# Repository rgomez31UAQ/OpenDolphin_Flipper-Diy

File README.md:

🐬 OpenDolphin

A fully open-source hardware implementation inspired by Flipper Zero.

Welcome to OpenDolphin! This repository contains the PCB design files, schematics, and Bill of Materials (BOM) for a DIY, Flipper Zero-compatible multi-tool. Designed by Dolphinos27.
Overview
This project is currently under active development

⚠️ Disclaimer

This project is for educational and research purposes only. The author (Dolphinos27) is not responsible for any misuse or damage caused by this device. Please comply with your local radio frequency and digital privacy laws.
📜 License

This project is licensed under the MIT License - see the LICENSE file for details.

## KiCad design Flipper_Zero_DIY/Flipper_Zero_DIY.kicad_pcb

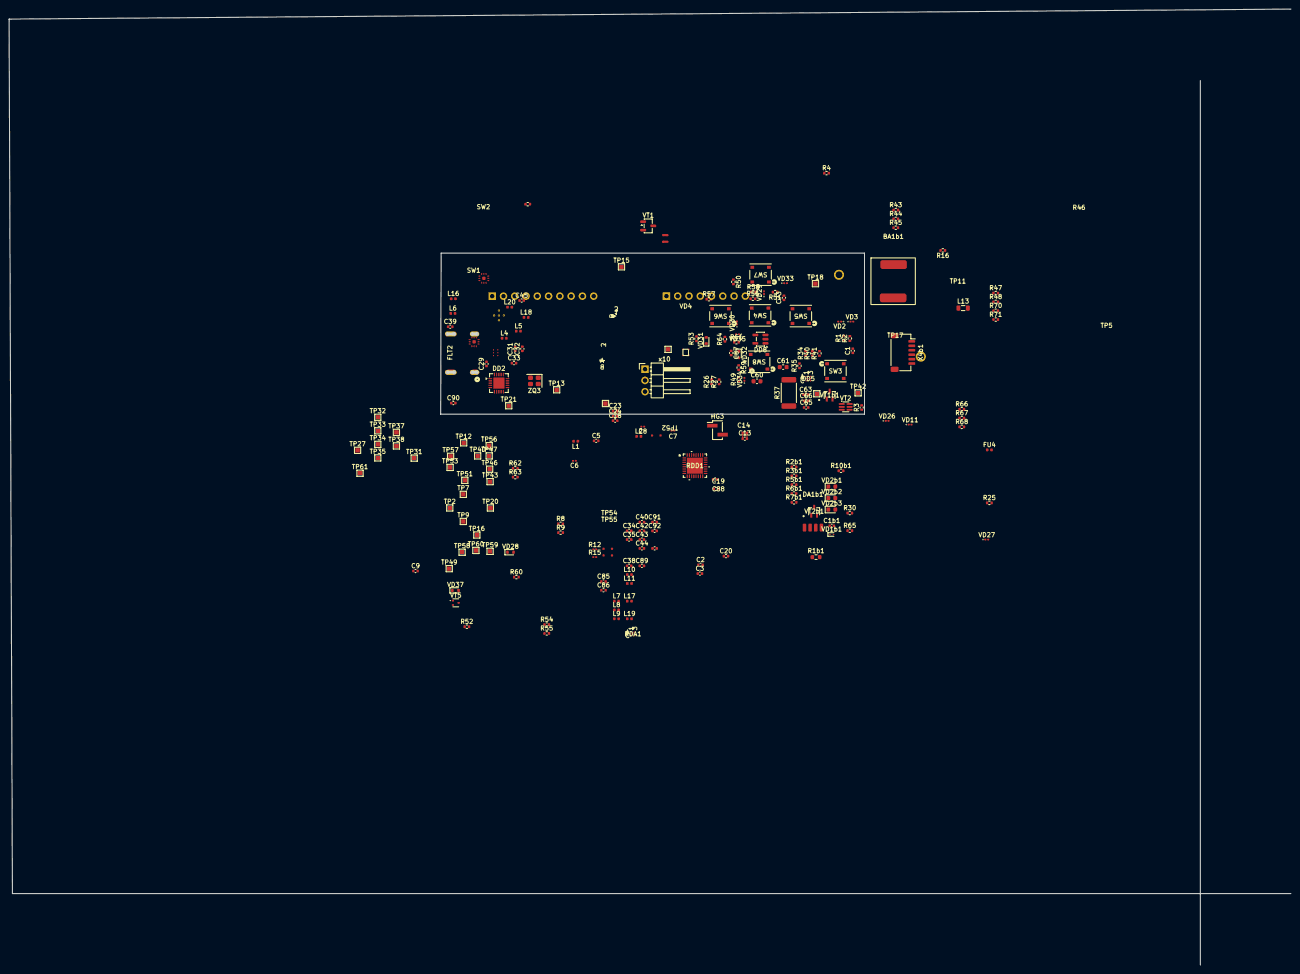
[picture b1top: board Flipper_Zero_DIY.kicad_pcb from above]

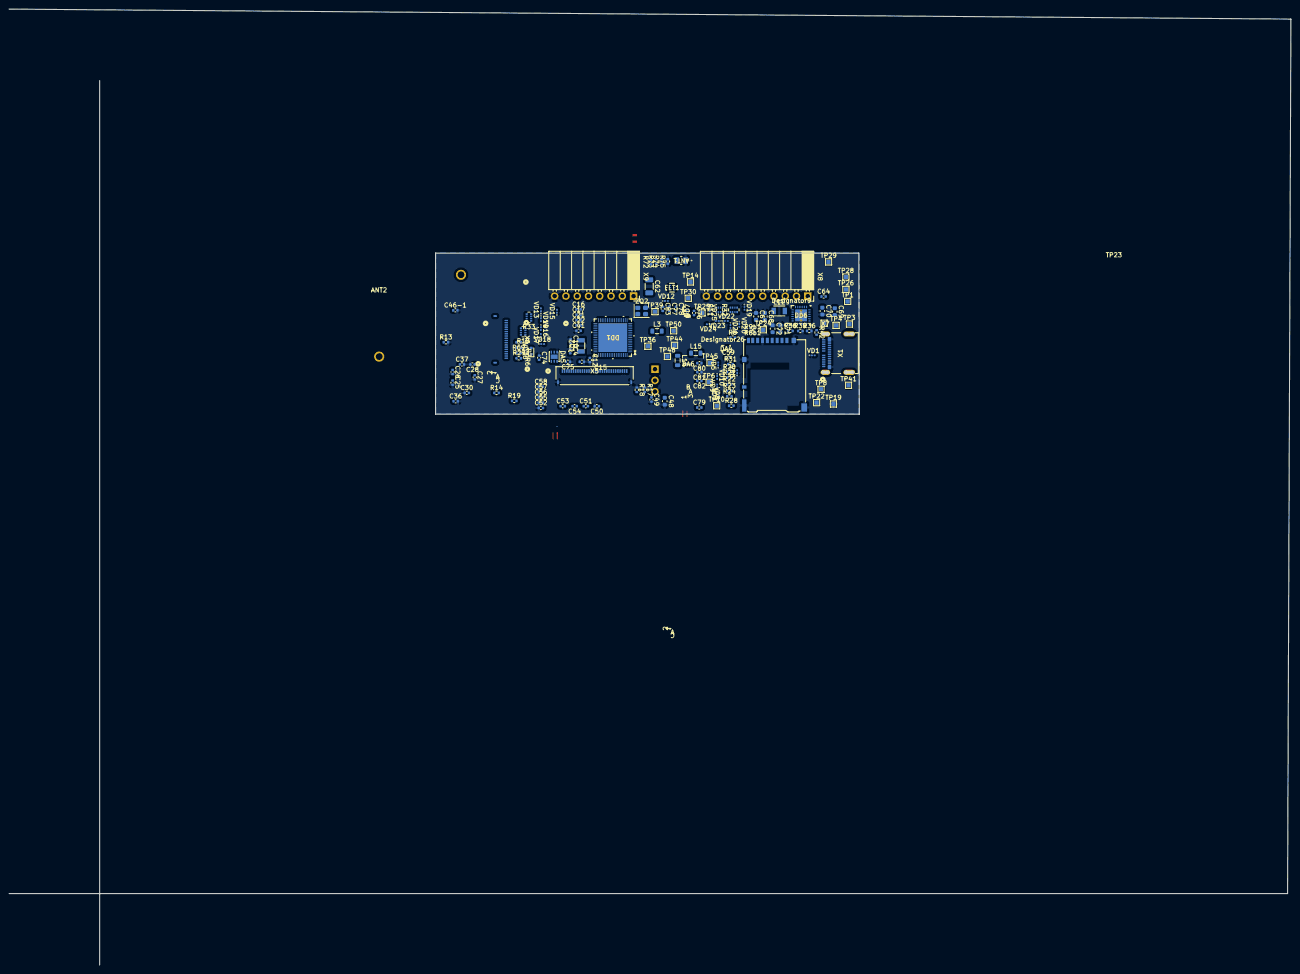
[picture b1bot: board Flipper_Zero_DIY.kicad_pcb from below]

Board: 2 copper layers, 288.8 x 215.3 mm, 342 parts (144 on the bottom side), 195 nets.

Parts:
ANT1: 1001312; ANT_1001312_AVX
ANT2: Sub-1GHz Antenna A5; Antenna_2
BA1b1: AST0760MCTRQ; Buzzer_539-AST0760MCTRQ
C1, C1b1, C12, C13, C14, C18, C22, C24, C25, C26, C27, C28, C30, C36, C37, C41, C49, C85, C88: 100nF; C_0402_1005Metric
C2, C3, C31, C39, C40, C44, C50, C51, C52, C53, C55, C56, C57, C58, C89, C90, C92: DNP; C_0402_1005Metric
C4, C10: 18pF; C_0402_1005Metric
C5: 0.8pF; C_0402_1005Metric
C6: 0.3pF; C_0201_0603Metric
C7: 1.5pF; C_0201_0603Metric
C8: DNP; C_0201_0603Metric
C9, C80, C83, C86, C87: 10uF; C_0402_1005Metric
C15, C19, C20, C73, C77, C81: 4.7uF; C_0402_1005Metric
C16, C21, C59, C63, C74, C75: 1uF; C_0402_1005Metric
C17: 10nF; C_0402_1005Metric
C23, C29, C38, C46-1, C46-2: 100pF; C_0402_1005Metric
C32: 1.2pF; C_0402_1005Metric
C33: 0.6pF; C_0402_1005Metric
C34, C35: 9pF; C_0402_1005Metric
C42, C43: 10pF; C_0402_1005Metric
C45: 8.2pF; C_0402_1005Metric
C48, C60, C61, C67, C68, C70, C71, C72: 10uF; C_0603_1608Metric
C54, C66, C76, C78, C79, C82: 2.2uF; C_0402_1005Metric
C62: DNP; C_1206_3216Metric
C64: 47nF; C_0402_1005Metric
C65: 470nF; C_0402_1005Metric
C69: 1uF; C_0603_1608Metric
C91: 22pF; C_0402_1005Metric
DA1b1: TSOP75338TR
DA4: LP5562TMX/NOPB; LP5562TMX-NOPB
DA5: ADP151ACPZ-3.3-R7; LFCSP-6-1EP_2x2mm_P0.65mm_EP1x1.6mm
DA6: LM3281YFQR
DD1: STM32WB55RGV6TR
DD2: QFN-20-1EP_4x4mm_P0.5mm_EP2.5x2.5mm
DD5: BQ27220YZFR
DD6: BQ25896RTWR
DD7: LM3281YFQR
DD8: NC7SZ125M5X; SOT-23-5
FLT1: LFL182G45TC1A108
FLT2: B0310J50100AHF; 0805_6PIN_PACKAGE
FU4: ERB-RD2R00X; Fuse_0402_1005Metric
HG3: ERC12864FAMF03-1-S7; PinHeader_1x02_P2.00mm_Vertical_SMD_Pin1Left
L1, L11: 2.7nH; L_0402_1005Metric
L2: 3nH; L_0402_1005Metric
L3: 10uH; L_0805_2012Metric
L4: 3.3nH; L_0402_1005Metric
L5: 6.8nH; L_0402_1005Metric
L6, L7, L8, L18, L20: 0; L_0402_1005Metric
L9: 2.2nH; L_0402_1005Metric
L10: DNP; L_0402_1005Metric
L12: 1uH; L_TDK_NLV25_2.5x2.0mm
L13, L14, L15: 470nH; L_0805_2012Metric
L16: 56nH; L_0402_1005Metric
L17: 22nH; L_0402_1005Metric
L19: 27nH; L_0402_1005Metric
R1, R2: 5.1k; R_0402_1005Metric
R1b1: 22; R_0603_1608Metric
R2b1, R6b1, R23, R31: 150; R_0402_1005Metric
R3: 100k; C_0402_1005Metric
R3b1, R8b1, R34, R35, R44, R46, R47, R49, R50, R51, R53, R61, R62: 10k; R_0402_1005Metric
R4, R60, R64: 100k; R_0402_1005Metric
R5, R17, R18, R43, R52, R65, R66, R67, R73, R74, R75: DNP; R_0402_1005Metric
R5b1, R9b1, R10b1: 39; R_0402_1005Metric
R6, R7, R24, R26, R28, R29: 51; R_0402_1005Metric
R7b1: 10; R_0402_1005Metric
R8, R9: 22; R_0402_1005Metric
R10, R11, R32, R33: 51; R_Array_Convex_4x0402
R12, R15: 0; R_0201_0603Metric
R13: 56k; R_0402_1005Metric
R14, R54, R55, R56, R57, R58, R59: 330; R_0402_1005Metric
R16, R70: 1.5; R_0402_1005Metric
R19, R20, R25, R27, R30, R72: 0; R_0402_1005Metric
R21, R22, R68: 47k; R_0402_1005Metric
R36: 470; R_0402_1005Metric
R37: 10m; R_2512_6332Metric
R38: 5.23k; R_0402_1005Metric
R39: 30.1k; R_0402_1005Metric
R40, R41: 1.5k; R_0402_1005Metric
R42: 4.7k; R_0402_1005Metric
R45: 100; R_0402_1005Metric
R48, R71: 3.3; R_0402_1005Metric
R63: 510; R_0402_1005Metric
R69: 1k; R_0402_1005Metric
RDA1: FAN48610BUC50X; WLCSP9_1P2X1P2_ONS
RDD1: ST25R3916-AQWT; VFQFPN32_5X5_WETTABLE_STM
SB5, SB6: Net Tie; NetTie-2_SMD_Pad0.5mm
SW1: SKY13373-460LF; QFN-12-2x2mm_equal_distribution
SW2: QFN-12-2x2mm_equal_distribution
SW3, SW4, SW5, SW6, SW7, SW8: SKRMAAE010; SKRMAAE010_AAL
TP1: STAT; TestPoint_Pad_1.0x1.0mm
TP2: PG; TestPoint_Pad_1.0x1.0mm
TP3: PWR_INT; TestPoint_Pad_1.0x1.0mm
TP4: OTG; TestPoint_Pad_1.0x1.0mm
TP5: GPOUT; TestPoint_Pad_1.0x1.0mm
TP6: TEMP; TestPoint_Pad_1.0x1.0mm
TP7: 3V32; TestPoint_Pad_1.0x1.0mm
TP8: 5V1; TestPoint_Pad_1.0x1.0mm
TP9: 5V2; TestPoint_Pad_1.0x1.0mm
TP10: BAT1; TestPoint_Pad_1.0x1.0mm
TP11: BAT2; TestPoint_Pad_1.0x1.0mm
TP12: SYS1; TestPoint_Pad_1.0x1.0mm
TP13: SYS2; TestPoint_Pad_1.0x1.0mm
TP14: EXT3V3; TestPoint_Pad_1.0x1.0mm
TP15: EXT3V32; TestPoint_Pad_1.0x1.0mm
TP16: LDO1; TestPoint_Pad_1.0x1.0mm
TP17: LDO2; TestPoint_Pad_1.0x1.0mm
TP18: GND1; TestPoint_Pad_1.0x1.0mm
TP19: GND2; TestPoint_Pad_1.0x1.0mm
TP20: GND3; TestPoint_Pad_1.0x1.0mm
TP21: GND4; TestPoint_Pad_1.0x1.0mm
TP22: I2C_SDA; TestPoint_Pad_1.0x1.0mm
TP23: I2C_SCL; TestPoint_Pad_1.0x1.0mm
TP24: SWDIO; TestPoint_Pad_1.0x1.0mm
TP25: SWCLK; TestPoint_Pad_1.0x1.0mm
TP26: I2C_SCL2; TestPoint_Pad_1.0x1.0mm
TP27: I2C_SDA2; TestPoint_Pad_1.0x1.0mm
TP28: UART1_RX; TestPoint_Pad_1.0x1.0mm
TP29: UART1_TX; TestPoint_Pad_1.0x1.0mm
TP30: VIBRO; TestPoint_Pad_1.0x1.0mm
TP31: NFC_CS; TestPoint_Pad_1.0x1.0mm
TP32: RFID_CARRIER; TestPoint_Pad_1.0x1.0mm
TP33: IR_RX; TestPoint_Pad_1.0x1.0mm
TP34, TP60: IR_TX; TestPoint_Pad_1.0x1.0mm
TP35, TP57: SPEAKER; TestPoint_Pad_1.0x1.0mm
TP36, TP59: iBTN; TestPoint_Pad_1.0x1.0mm
TP37: RFID_IN; TestPoint_Pad_1.0x1.0mm
TP38: RFID_OUT; TestPoint_Pad_1.0x1.0mm
TP39: RFID_PULL; TestPoint_Pad_1.0x1.0mm
TP40: R_CLK; TestPoint_Pad_1.0x1.0mm
TP41: VBUS1; TestPoint_Pad_1.0x1.0mm
TP42: VBUS2; TestPoint_Pad_1.0x1.0mm
TP43: D-; TestPoint_Pad_1.0x1.0mm
TP44: D+; TestPoint_Pad_1.0x1.0mm
TP45: D_MI; TestPoint_Pad_1.0x1.0mm
TP46: R_MI; TestPoint_Pad_1.0x1.0mm
TP47: R_MO; TestPoint_Pad_1.0x1.0mm
TP48: D_MO; TestPoint_Pad_1.0x1.0mm
TP49: D_SCK; TestPoint_Pad_1.0x1.0mm
TP50: BOOT; TestPoint_Pad_1.0x1.0mm
TP51: NRST; TestPoint_Pad_1.0x1.0mm
TP52: BLE1; 2_TEST_PIN_1.35mm_pitch
TP53: CC_PWR; TestPoint_Pad_1.0x1.0mm
TP54: Balun; 2_TEST_PIN_1.35mm_pitch
TP55: SUB-1-GHz; 2_TEST_PIN_1.35mm_pitch
TP56: SYS; TestPoint_Pad_1.0x1.0mm
TP58: SPEAKER1; TestPoint_Pad_1.0x1.0mm
TP61: GND; TestPoint_Pad_1.0x1.0mm
VD1, VD2, VD3, VD11, VD13, VD14, VD15, VD16, VD17, VD18, VD19, VD20, VD21, VD22, VD23, VD24, VD25: ESD230B1W0201E6327XTSA1; D_0201_0603Metric
VD1b1: ESD230B1W0201E6327XT; D_SOD-923
VD2b1, VD2b2, VD2b3: VSMY14940; LED_0603_1608Metric
VD4: CLMUD-FKC-CHJNPM569ABB845343; SMD_RGB_LED_CLMUD-FKC-CHJNPM569ABB845343
VD5, VD6, VD7, VD8, VD9, VD10, VD12, VD26, VD27, VD29, VD30, VD33, VD34, VD35: ESD241B1W0201E6327XTSA1; D_0201_0603Metric
VD28, VD31, VD32: 1N4148X; D_SOD-523
VD36: 1N4148X-TP; D_SOD-523
VD37: DNP; D_SOD-523
VT1: DMP1045U-7; SOT-23-3
VT1b1, VT2b1: DMN2058UW-7; SOT323_DMN2058UW_DIO
VT2: MMDT2907A-7-F; SOT-363_SC-70-6
VT5: DMN313DLT-7; SOT-523
X1: 105450-0101; CONN_105450-0101_MOL
X4b1: 0.5-H2.0-6LT; JST_SH_SM06B-SRSS-TB_1x06-1MP_P1.00mm_Horizontal
X5: FH34SRJ-30S-0.5SH(50); CONN30x1_FH34SRJ-30S-0.5SH50_HIR
X6: FH34SRJ-18S-0.5SH(50); 18_pin_JST
X7: Micro_SD; microSD_HC_Hirose_DM3AT-SF-PEJM5
X8: 2.54-WT-1X10; PinSocket_1x10_P2.54mm_Horizontal
X9: 2.54-WT-1X8; PinSocket_1x08_P2.54mm_Horizontal
ZQ1: SF32K32768D31T-12.5; Crystal_SMD_3215-2Pin_3.2x1.5mm
ZQ2: CXD2-032000000-1010B; Crystal_SMD_2520-4Pin_2.5x2.0mm
ZQ3: CXD2-026000000-0810B; Crystal_SMD_2520-4Pin_2.5x2.0mm
x10: Connector 3P; PinHeader_1x03_P2.54mm_Horizontal

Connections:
+3V3: C9.2, C12.1, C13.1, C14.1, C15.1, C16.1, C17.1, C18.1, C19.1, C23.1, C24.1, C25.1, C26.1, C27.1, C28.1, C36.1, C37.1, C48.1, C49.1, C85.1, C88.1, DD1.14 (VDDA), DD1.30 (VDD), DD1.33 (VDDRF), DD1.44 (VDDSMPS), DD1.45 (VDD), DD1.55 (VDDUSB), DD1.68 (VDD), DD2.4 (DVDD), DD2.9 (AVDD), DD2.11 (AVDD), DD2.14 (AVDD), DD2.15 (AVDD), DD2.18 (DGUARD), DD8.5 (VCC), R5.2, R34.1, R40.1, R41.1, R42.1, R47.1, R48.2, R49.2, R50.2, R51.2, R52.2, R53.2, R62.2, R71.2, RDD1.1 (VDD_IO), SW1.6 (VDD), SW2.6 (VDD), SW4.2, TP7.1, TP53.1, VD26.2 (A2), X5.5, X5.6, X5.7, X5.8, X5.9, X5.10, X5.11, X5.12, X5.15, X6.3
+5V: RDA1.A1 (VOUT), RDA1.A2 (VOUT), RDD1.8 (VDD), RDD1.10 (VDD_TX)
BAT: C63.2, DD5.C1 (SRP), DD5.C3 (BAT), R37.2, TP10.1, TP11.1, x10.1
BUTTON_BACK: DD1.2 (PC13), DD6.12 (QON_N), R54.1
BUTTON_DOWN: DD1.50 (PC6), R59.1
BUTTON_LEFT: DD1.29 (PB11), R57.1
BUTTON_OK: DD1.5 (PH3), R55.1, TP50.1
BUTTON_RIGHT: DD1.46 (PB12), R56.1
BUTTON_UP: DD1.28 (PB10), R58.1
CC1101_CS: DD1.61 (PD0), DD2.7 (CSN)
CC1101_G0: DD1.16 (PA1), R14.2
DISPLAY_CS: DD1.59 (PC11), R17.2, X5.2
DISPLAY_DI: DD1.39 (PB1), X5.4
DISPLAY_RST: DD1.38 (PB0), R18.2, X5.3
GND: ANT1.1 (A), C1.2, C1b1.2, C2.1, C3.1, C4.1, C5.2, C6.2, C7.2, C8.1, C8.2, C9.1, C10.1, C12.2, C13.2, C14.2, C15.2, C16.2, C17.2, C18.2, C19.2, C20.2, C21.2, C22.2, C23.2, C24.2, C25.2, C26.2, C27.2, C28.2, C30.1, C31.2, C32.2, C34.1, C35.1, C36.2, C37.2, C39.1, C40.1, C41.1, C42.2, C43.2, C44.2, C45.2, C46-1.2, C46-2.2, C48.2, C49.2, C50.2, C52.1, C55.1, C56.1, C57.1, C58.1, C59.2, C60.1, C61.1, C63.1, C65.1, C66.1, C67.1, C68.1, C69.2, C70.2, C71.1, C72.1, C73.1, C74.1, C75.1, C77.1, C80.1, C81.1, C83.1, C85.2, C86.2, C87.2, C88.2, C89.1, C90.2, C91.2, C92.2, DA1b1.1 (GND), DA1b1.4 (GND), DA4.A3 (CLK_32K), DA4.B1 (ADDR_SEL1), DA4.B2 (ADDR_SEL0), DA4.B3 (GND), DA5.1 (GND), DD1.32 (VSSRF), DD1.42 (VSSSMPS), DD1.69 (EPAD), DD2.16 (GND), DD2.19 (GND), DD2.21 (EPAD), DD5.B2 (VSS), DD6.2 (PSEL), DD6.9 (CE_N), DD6.17 (PGND), DD6.18 (PGND), DD6.25 (PAD), DD8.3 (GND), FLT1.2 (GND), FLT1.5 (GND), FLT2.2 (GND), L2.2, L10.1, R1.2, R2.2, R3.1, R3b1.1, R4.1, R8b1.1, R13.2, R17.1, R18.1, R35.2, R36.2, R39.2, R43.1, R46.2, R61.1, R72.1, R72.2, R74.1, R74.2, R75.1, R75.2, RDA1.C1 (PGND), RDA1.C2 (PGND), RDA1.C3 (AGND), RDD1.6 (GND_D), RDD1.12 (GND_DR), RDD1.16 (GND_DR), RDD1.20 (I2C_EN), RDD1.21 (VSS), RDD1.26 (GND_A), RDD1.33 (EPAD), SB5.2, SB6.2, SW1.2 (GND), SW1.7 (GND), SW1.8 (GND), SW1.10 (GND), SW1.12 (GND), SW2.2 (GND), SW2.7 (GND), SW2.8 (GND), SW2.10 (GND), SW2.12 (GND), SW3.2, SW5.2, SW6.2, SW7.2, SW8.2, TP18.1, TP19.1, TP20.1, TP21.1, TP52.2, TP54.2, TP55.2, TP61.1, VD1.1 (A1), VD1b1.1 (A1), VD2.1 (A1), VD3.1 (A1), VD5.1 (A1), VD6.1 (A1), VD7.1 (A1), VD8.1 (A1), VD9.1 (A1), VD10.1 (A1), VD12.1 (A1), VD13.1 (A1), VD14.1 (A1), VD15.1 (A1), VD16.1 (A1), VD17.1 (A1), VD18.1 (A1), VD19.1 (A1), VD20.1 (A1), VD21.1 (A1), VD22.1 (A1), VD23.1 (A1), VD24.1 (A1), VD25.1 (A1), VD26.1 (A1), VD27.2 (A2), VD29.2 (A2), VD30.2 (A2), VD33.2 (A2), VD34.2 (A2), VD35.2 (A2), VT1b1.3 (S), VT2b1.3 (S), VT5.3 (S), X1.A1 (GND), X1.A12 (GND), X1.B1 (GND), X1.B12 (GND), X4b1.1, X5.16, X5.28, X5.29, X5.31, X5.32, X6.6, X6.8, X7.6 (VSS), X7.11 (SHIELD), X8.3, X8.10, X9.8, ZQ2.3, ZQ3.3, x10.3
GND1: C79.1, C82.1, DA6.A3 (EPAD), SB5.1
GND2: C76.1, C78.1, DD7.A3 (GND), SB6.1
I2C_SCL: DA4.C2 (SCL), DD1.24 (PA9), DD5.A3 (SCL), DD6.5 (SCL), R41.2, TP23.1
I2C_SDA: DA4.C1 (SDA), DD1.51 (PA10), DD5.A2 (SDA), DD6.6 (SDA), R40.2, TP22.1
IR_RX: DD1.15 (PA0), TP33.1, X6.17
IR_TX: DD1.7 (PB9), TP34.1, X6.16
LCD_LED: DA4.A1 (W), HG3.2
LDO_3.3V: C75.2, DA5.2 (VOUT), DD1.1 (VBAT), TP16.1, TP17.1
NFC_CS: DD1.40 (PE4), RDD1.29 (BSS), TP31.1, X6.4
unnamed: ANT2.1 (A), C90.1, R15.2, TP55.1
unnamed: BA1b1.2, R1b1.1
unnamed: C29.2, FLT2.3 (Bal)
unnamed: C31.1, L4.2, L5.1
unnamed: C32.1, L5.2, R12.1
unnamed: C38.2, FLT2.4 (Bal)
unnamed: C39.2, L6.1, L18.2
unnamed: C42.1, L7.2, L19.1
unnamed: C43.1, L8.1, L19.2
unnamed: C44.1, L9.2, R15.1
unnamed: C45.1, L11.1, L20.2
unnamed: C64.2, DD6.19 (SW), DD6.20 (SW), L12.1
unnamed: C89.2, L6.2, L16.1
unnamed: C91.1, L8.2, L17.1
unnamed: DA1b1.3 (OUT), X4b1.2
unnamed: C1b1.1, DA1b1.2 (Vs), R7b1.1
unnamed: DA4.A4 (B), R30.1
unnamed: DA4.B4 (G), R27.1
unnamed: DA4.C4 (R), R25.1
unnamed: C71.2, C72.2, C74.2, DA5.3 (VIN), DD5.C2 (SRN), DD6.13 (BAT), DD6.14 (BAT), R37.1
unnamed: C80.2, C81.2, C82.2, DA6.A1 (FB), L15.1, R16.2, R70.2
unnamed: DA6.B2 (SW), L14.1
unnamed: DD1.35 (OSC_IN), ZQ2.1
unnamed: DD1.34 (OSC_OUT), ZQ2.2
unnamed: DD1.20 (PA5), R6.2
unnamed: DD1.52 (PA11), R8.2, TP43.1
unnamed: DD1.53 (PA12), R5.1, R9.2, TP44.1
unnamed: DD1.65 (PB5), R7.1
unnamed: C4.2, DD1.3 (PC14), ZQ1.2
unnamed: C10.2, DD1.4 (PC15), ZQ1.1
unnamed: C5.1, DD1.31 (RF1), L1.1
unnamed: C20.1, DD1.41 (VFBSMPS), L3.1
unnamed: DD1.43 (VLXSMPS), L3.2
unnamed: C21.1, C22.1, DD1.13 (VREF+)
unnamed: C30.2, DD2.5 (DCOUPL)
unnamed: DD2.6 (GDO0), R14.1
unnamed: DD2.17 (RBIAS), R13.1
unnamed: C29.1, C33.1, DD2.13 (RF_N)
unnamed: C33.2, C38.1, DD2.12 (RF_P)
unnamed: C34.2, DD2.8 (XOSC_Q1), ZQ3.1
unnamed: C35.2, DD2.10 (XOSC_Q2), ZQ3.2
unnamed: DD5.B1 (BIN), R35.1
unnamed: DD5.A1 (GPOUT), R34.2, TP5.1
unnamed: C65.2, C66.2, DD5.B3 (VDD)
unnamed: C64.1, DD6.21 (BTST)
unnamed: DD6.10 (ILIM), R36.1
unnamed: DD6.7 (INT), R42.2, TP3.1
unnamed: DD6.8 (OTG_IUSB), R44.2, TP4.1, VT5.1 (D)
unnamed: DD6.3 (PG_N), TP2.1
unnamed: C70.1, DD6.23 (PMID)
unnamed: C73.2, DD6.22 (REGN), R38.1
unnamed: DD6.4 (STAT), TP1.1
unnamed: DD6.11 (TS), R38.2, R39.1, R43.2, TP6.1, x10.2
unnamed: DD7.B2 (SW), L13.1
unnamed: C86.1, DD8.1 (IN1), R60.1, VD28.1 (K)
unnamed: C87.1, DD8.2 (IN2), R64.1, VD31.1 (K)
unnamed: DD8.4 (OUT), VD32.1 (K)
unnamed: C6.1, FLT1.1 (IN), L1.2
unnamed: C7.1, FLT1.3 (OUT), L2.1, TP52.1
unnamed: FLT2.1 (Unbal), L4.1
unnamed: HG3.1, R19.2
unnamed: L14.2, R16.1, R70.1
unnamed: L15.2, R48.1, R71.1
unnamed: R10.3 (R2.2), X9.2
unnamed: R10.4 (R3.2), X9.3
unnamed: R11.2 (R1.2), X8.2
unnamed: R11.3 (R2.2), X8.4
unnamed: R11.5 (R4.2), TP29.1, X8.5
unnamed: R32.2 (R1.2), TP28.1, X8.6
unnamed: R32.3 (R2.2), TP27.1, X8.7
unnamed: R32.4 (R3.2), TP26.1, X8.8
unnamed: R32.5 (R4.2), X8.9
unnamed: R33.2 (R1.2), X9.4
unnamed: R33.3 (R2.2), X9.5
unnamed: R33.4 (R3.2), X9.6
unnamed: R33.5 (R4.2), X9.7
unnamed: RDA1.B1 (SW), RDA1.B2 (SW)
unnamed: RDD1.9 (VDD_RF), RDD1.14 (VDD_DR)
unnamed: L18.1, SW1.1 (J1)
unnamed: L7.1, SW1.9 (J2)
unnamed: L20.1, SW1.3 (J3)
unnamed: R12.2, SW1.11 (RFin), TP54.1
unnamed: L17.2, SW2.1 (J1)
unnamed: L16.2, SW2.9 (J2)
unnamed: C92.1, L11.2, SW2.3 (J3)
unnamed: C40.2, L9.1, L10.2, SW2.11 (RFin)
unnamed: R8.1, VD2.2 (A2), X1.A7 (D1-), X1.B7 (D2-)
unnamed: R9b1.1, VD2b1.2 (A)
unnamed: VD2b1.1 (K), VD2b2.1 (K), VD2b3.1 (K), VT2b1.1 (D)
unnamed: R10b1.1, VD2b2.2 (A)
unnamed: R5b1.1, VD2b3.2 (A)
unnamed: R9.1, VD3.2 (A2), X1.A6 (D1+), X1.B6 (D2+)
unnamed: R30.2, VD4.2 (BK)
unnamed: R27.2, VD4.3 (GK)
unnamed: R25.2, VD4.4 (RK)
unnamed: C60.2, C61.2, R20.1, R21.2, R22.2, R65.2, R66.2, R67.2, R68.2, VD6.2 (A2), X7.4 (VDD)
unnamed: C62.2, VD11.1 (A1)
unnamed: R52.1, R54.2, R60.2, SW3.1, VD27.1 (A1), VD28.2 (A)
unnamed: R51.1, R56.2, SW5.1, VD29.1 (A1)
unnamed: R53.1, R57.2, R64.2, SW6.1, VD30.1 (A1), VD31.2 (A)
unnamed: R63.2, VD32.2 (A)
unnamed: R50.1, R58.2, SW7.1, VD33.1 (A1)
unnamed: R49.1, R59.2, SW8.1, VD34.1 (A1)
unnamed: R55.2, R61.2, SW4.1, VD35.1 (A1)
unnamed: R69.1, VD36.1 (K)
unnamed: R3.2, VD37.2 (A), VT2.2 (B1), VT2.3 (C2), VT2.5 (B2)
unnamed: R4.2, VT1.2 (G), VT2.6 (C1)
unnamed: BA1b1.1, TP58.1, VT1b1.1 (D)
unnamed: R2b1.2, R3b1.2, VT1b1.2 (G)
unnamed: R6b1.1, R8b1.2, VT2b1.2 (G)
unnamed: R45.2, R46.1, VT5.2 (G)
unnamed: R1.1, X1.A5 (CC1)
unnamed: R2.1, X1.B5 (CC2)
unnamed: R6b1.2, TP60.1, X4b1.3
unnamed: R2b1.1, TP57.1, X4b1.5
unnamed: C50.1, X5.17
unnamed: C51.1, X5.18
unnamed: C51.2, C54.1, X5.19
unnamed: C54.2, X5.20
unnamed: C53.1, X5.21
unnamed: C53.2, X5.22
unnamed: C52.2, X5.23
unnamed: C55.2, X5.24
unnamed: C56.2, X5.25
unnamed: C57.2, X5.26
unnamed: C58.2, X5.27
unnamed: R29.2, X6.9
unnamed: R26.2, X7.5 (CLK)
unnamed: R24.2, X7.3 (CMD)
unnamed: R28.2, X7.7 (DAT0)
unnamed: R21.1, X7.8 (DAT1)
unnamed: R22.1, X7.1 (DAT2)
unnamed: R23.1, X7.2 (DAT3/CD)
unnamed: R31.2, X7.10 (SW_DTCT)
unnamed: C62.1, FU4.2, X9.1
PA4: DD1.19 (PA4), R33.1 (R1), VD16.2 (A2)
PA6: DD1.21 (PA6), R10.1 (R1), VD17.2 (A2)
PA7: DD1.22 (PA7), VD18.2 (A2)
PB2: DD1.27 (PB2), VD14.2 (A2)
PB3: DD1.63 (PB3), VD15.2 (A2)
PC0: DD1.9 (PC0), R32.1 (R1), VD20.2 (A2)
PC1: DD1.10 (PC1), VD21.2 (A2)
PC3: DD1.12 (PC3), VD13.2 (A2)
PERIPH_POWER: DD1.18 (PA3), DD7.B3 (EN), R47.2
Pogo Pin 1: TP59.1, VD1b1.2 (A2), X4b1.4
RESET: C41.2, DA4.C3 (EN_VCC), DD1.8 (NRST), R62.1, R63.1, TP51.1
RFID_CARRIER: DD1.56 (PA15), TP32.1, X6.18
RFID_OUT: DD1.47 (PB13), TP38.1, X6.12
RFID_PULL: DD1.17 (PA2), TP39.1, X6.11
RFID_RF_IN: DD1.26 (PC5), TP37.1, X6.5
RF_SW_0: C46-2.1, DD1.25 (PC4), SW1.5 (V2), SW2.4 (V1)
RF_SW_1: C46-1.1, DD2.3 (GD02), SW1.4 (V1), SW2.5 (V2)
SD_CD: DD1.58 (PC10), R31.1, R68.1, VD5.2 (A2)
SD_CS: DD1.60 (PC12), R23.2, VD10.2 (A2)
SPEAKER: DD1.6 (PB8), TP35.1, X6.15
SPI_D_MISO: DD1.11 (PC2), R28.1, R65.1, TP45.1, VD7.2 (A2)
SPI_D_MOSI: C2.2, DD1.49 (PB15), R24.1, R67.1, TP48.1, VD9.2 (A2), X5.14
SPI_D_SCK: C3.2, DD1.62 (PD1), R26.1, R66.1, TP49.1, VD8.2 (A2), X5.13
SPI_R_MISO: DD1.64 (PB4), DD2.2 (SO), R29.1, RDD1.32 (MISO/SDA), TP46.1
SPI_R_MOSI: DD2.20 (SI), R7.2, RDD1.31 (MOSI), TP47.1, X6.13
SPI_R_SCK: DD2.1 (SCLK), R6.1, RDD1.30 (SCLK/SCL), TP40.1, X6.7
SWCLK: R11.1 (R1), TP25.1, VD25.2 (A2)
SWDIO: DD1.54 (PA13), TP24.1, VD24.2 (A2)
SYS: C59.1, C67.2, C68.2, C76.2, C79.2, DA4.A2 (VDD), DA6.A2 (VIN), DA6.B1 (MODE), DA6.B3 (EN), DD6.15 (SYS), DD6.16 (SYS), DD7.A2 (VIN), DD7.B1 (MODE), L12.2, R1b1.2, R5b1.2, R7b1.2, R9b1.2, R10b1.2, R19.1, R44.1, RDA1.A3 (VIN), RDA1.B3 (EN), TP12.1, TP13.1, TP56.1, VD4.1 (A), X4b1.6, X6.1, X6.2
UART1_RX: DD1.67 (PB7), VD22.2 (A2)
UART1_TX: DD1.66 (PB6), VD23.2 (A2)
USB 5V: C69.1, DD6.1 (VBUS), FU4.1, TP8.1, TP9.1, VD11.2 (A2), VD36.2 (A), VT1.3 (S), VT2.1 (E1)
VBUS: C1.1, R45.1, TP41.1, TP42.1, VD1.2 (A2), VD37.1 (K), VT1.1 (D), VT2.4 (E2), X1.A4 (VBUS), X1.A9 (VBUS), X1.B4 (VBUS), X1.B9 (VBUS)
VIBRO: DD1.23 (PA8), TP30.1, X6.10
ext3.3V: C77.2, C78.2, C83.2, DD7.A1 (FB), L13.2, R20.2, TP14.1, TP15.1, VD12.2 (A2), X8.1
iBTN: DD1.48 (PB14), R69.2, TP36.1, VD19.2 (A2), X6.14

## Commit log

2026-02-03 README.md
